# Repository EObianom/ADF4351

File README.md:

# ADF4351 Arduino Library & KiCad Hardware Design
| KiCad Hardware PCB Design | Software Output / RF Spectrum |
| :---: | :---: |
|  | https://github.com/user-attachments/assets/13627ffa-e069-458c-9974-3c6d26c1047d |

A complete open-source RF signal generation suite featuring a **lightweight C++ driver** and a **custom open-hardware PCB design in KiCad** for the Analog Devices ADF4351 wideband frequency synthesizer (35 MHz – 4.4 GHz).

### What This Project Provides
1. Software (Arduino Driver & Math Engine)
    - Register Calculation Engine: Automatically solves the complex Phase-Locked Loop (PLL) math to determine exact 32-bit values for hardware registers $R_0$ through $R_5$ across both Fractional-N and Integer-N modes.
    - Automatic Scaling: Handles RF output dividers (/1 to /64), dual-modulus prescalers (4/5 or 8/9), and GCD fraction reduction behind the scenes.
    - Hardware-Agnostic C++: Contains no hardcoded hardware SPI pins or board-specific hooks. Works seamlessly across all Arduino architectures, including AVR, ESP32, STM32, RP2040, Teensy, and SAMD, using standard SPI.h.
2. Hardware (KiCad Design Files)
    - Open Hardware Files: Complete schematics (.kicad_sch), 4-layer impedance-controlled PCB layouts (.kicad_pcb), and project files created in KiCad.
    - RF Output Network: Designed with proper high-frequency decoupling, low-noise power regulation, optimized loop filtering, and 50 Ω matched RF output traces with SMA connectivity for clean signal generation across the 35 MHz – 4.4 GHz spectrum.

## Table of Contents
- Features
- Installation
- Quick Start
- API Reference & Keyword Usage
  - Core Datatypes & Classes
  - Core Functions
  - Bulk Configuration
  - Register 5 Setters (Lock Detect & Initialization)
  - Register 4 Setters (RF Output & Power Controls)
  - Register 3 Setters (Clock Dividers & Modes)
  - Register 2 Setters (PLL & Charge Pump Controls)
  - Register 1 & 0 Setters (Prescaler & Phase Settings)
- Hardware Design & Variants
- Hardware Files & Production Assets
- License

## Features
- **Platform Agnostic:** Pure software calculation engine with zero hardware or architecture dependencies.
- **Dynamic PLL Solver:** Automates INT, FRAC, and MOD calculations with automated Euclidean GCD fraction reduction.
- **VCO & Divider Scaling:** Dynamically selects RF output dividers (/1 to /64) and prescalers (4/5 vs. 8/9).
- **Integrated Bitmask Safety:** All parameter setters perform bitwise masking to prevent register corruption.
- **KiCad Open Hardware Included:** Includes full schematic, PCB layout, and gerber files in the `hardware/` directory.

## Installation
### Via Arduino Library Manager
1. Open the Arduino IDE.
2. Go to Sketch → Include Library → Manage Libraries...
3. Search for ADF4351 and click Install.

### Manual Installation
1. Download the latest release .zip from GitHub.
2. In the Arduino IDE, go to Sketch → Include Library → Add .ZIP Library...
3. Select the downloaded .zip file.

## Quick Start
~~~
#include <Arduino.h>
#include "ADF4351.h"

const int CS_PIN = 10;
ADF4351 adf;

// Helper function to send 32-bit register words over hardware SPI
void writeRegister(uint32_t regData) {
    digitalWrite(CS_PIN, LOW);
    SPI.beginTransaction(SPISettings(5000000, MSBFIRST, SPI_MODE0));
    SPI.transfer32(regValue);
    SPI.endTransaction();
    digitalWrite(CS_PIN, HIGH);
    delayMicroseconds(1);
}

void setup() {
    Serial.begin(115200);
    pinMode(CS_PIN, OUTPUT);
    digitalWrite(CS_PIN, HIGH);
    SPI.begin();

    // 1. Configure synthesizer parameters (optional step; default is 25MHz ref clock)
    adf.setRefFreqHz(25000000);  // 25 MHz Reference
    adf.setOutputPower(3);       // +5 dBm Output Power

    // 2. Compute registers for target frequency (e.g., 433.92 MHz)
    uint32_t regs[6];
    if (adf.calculateRegisters(433920000ULL, regs)) {
        // Write registers R5 down to R0 in sequence (ADF4351 hardware requirement)
        for (int i = 5; i >= 0; i--) {
            writeRegister(regs[i]);
        }
        Serial.println(F("ADF4351 programmed successfully to 433.92 MHz!"));
    } else {
        Serial.println(F("Frequency target out of bounds or parameter error!"));
    }
}

void loop() {
    // Idle
}
~~~

## API Reference & Keyword Usage
### Core Datatypes & Classes
`ADF4351`

The primary class representing the ADF4351 synthesizer instance.
~~~
ADF4351 adf; // Instantiate with default configuration (25MHz TCXO/OCXO ref)
~~~
____
`Config`

A configuration structure containing all chip settings.
~~~
ADF4351::Config myConfig;
myConfig.refFreqHz = 10000000; // Set reference clock to 10 MHz
myConfig.outputPower = 2;      // Set power to +2 dBm
~~~

### Core Functions
`calculateRegisters(freqHz, outRegisters)`

Computes the 6 required 32-bit register values for a given frequency in Hertz.
- Parameters:
  - `freqHz (uint64_t)`: Target output frequency in Hz (35,000,000 to 4,400,000,000 Hz).
  - `outRegisters (uint32_t[6])`: Array to hold the resulting register words R0 through R5.
- Returns: bool – true if calculation succeeded; false if frequency is out of range or invalid.
~~~
uint32_t registers[6];
bool success = adf.calculateRegisters(1000000000ULL, registers); // 1.0 GHz
~~~

### Bulk Configuration
`setConfig(config)`

Overwrites the entire configuration struct in one operation.
~~~
ADF4351::Config cfg;
cfg.refFreqHz = 25000000;
cfg.outputPower = 3;
cfg.rfOutputEnable = 1;

adf.setConfig(cfg);
~~~
____
`getConfig()`

Retrieves the currently loaded configuration struct.
~~~
ADF4351::Config activeCfg = adf.getConfig();
Serial.print("Current Ref Freq: ");
Serial.println(activeCfg.refFreqHz);
~~~

### Individual Configuration Setting
#### Register 5 Setters
`setRefFreqHz(val)`

Sets the reference input frequency in Hz.
~~~
adf.setRefFreqHz(25000000); // 25 MHz Reference
~~~
___
`setLdPinMode(val)`

Configures the Lock Detect (LD) output pin mode (Bits [23:22], Mask: 0x03).
- 0: Low
- 1: Digital Lock Detect (Default)
- 2: Low
- 3: High
~~~
adf.setLdPinMode(1); // Digital Lock Detect
~~~

#### Register 4 Setters
`setFeedbackSelect(val)`

Selects VCO feedback signal source to N-counter (Bit [23], Mask: 0x01).
- 0: Divided (VCO output through divider)
- 1: Fundamental (VCO output directly; Default)
~~~
adf.setFeedbackSelect(1);
~~~
___
`setVcoPowerdown(val)`

Powers down the internal VCO (Bit [11], Mask: 0x01).
- 0: VCO Active
- 1: VCO Powered Down
~~~
adf.setVcoPowerdown(0);
~~~
___
`setMtld(val)`

Mute Till Lock Detect (Bit [10], Mask: 0x01).
- 0: Mute Disabled
- 1: Mute Enabled (RF output muted until PLL locks)
~~~
adf.setMtld(1);
~~~
___
`setAuxOutputSelect(val)`

Selects auxiliary RF output signal path (Bit [9], Mask: 0x01).
- 0: Divided Output
- 1: Fundamental Output
~~~
adf.setAuxOutputSelect(0);
~~~
___
`setAuxOutputEnable(val)`

Enables or disables auxiliary RF output pin (Bit [8], Mask: 0x01).
- 0: Disabled
- 1: Enabled
~~~
adf.setAuxOutputEnable(0);
~~~
___
`setAuxOutputPower(val)`

Configures auxiliary RF output power level (Bits [7:6], Mask: 0x03).
- 0: -4 dBm
- 1: -1 dBm
- 2: +2 dBm
- 3: +5 dBm
~~~
adf.setAuxOutputPower(0); // -4 dBm
~~~
___
`setRfOutputEnable(val)`

Main RF output power toggle (Bit [5], Mask: 0x01).
- 0: Output Disabled
- 1: Output Enabled
~~~
adf.setRfOutputEnable(1);
~~~
___
`setOutputPower(val)`

Sets main RF output power level (Bits [4:3], Mask: 0x03).
- 0: -4 dBm
- 1: -1 dBm
- 2: +2 dBm
- 3: +5 dBm
~~~
adf.setOutputPower(3); // +5 dBm maximum power
~~~

#### Register 3 Setters
`setBandSelectMode(val)`

Configures Band Select Clock logic mode (Bit [23], Mask: 0x01).
- 0: Low / Standard PFD frequency
- 1: High / Fast PFD frequency
~~~
adf.setBandSelectMode(0);
~~~
___
`setAbp(val)`

Anti-Backlash Pulse Width (Bit [22], Mask: 0x01).
- 0: 6 ns (Recommended for Fractional-N operation)
- 1: 3 ns (Recommended for Integer-N operation)
~~~
adf.setAbp(0);
~~~
___
`setChargeCancel(val)`

Charge pump cancellation control (Bit [21], Mask: 0x01).
- 0: Disabled
- 1: Enabled
~~~
adf.setChargeCancel(0);
~~~
___
`setCsr(val)`

Cycle Slip Reduction (Bit [18], Mask: 0x01).
- 0: Disabled
- 1: Enabled
~~~
adf.setCsr(0);
~~~
___
`setClkDivMode(val)`

Clock Divider Mode (Bits [16:15], Mask: 0x03).
- 0: Clock Divider Off
- 1: Fast Lock Enable
- 2: Resynchronization Enable
~~~
adf.setClkDivMode(0);
~~~
___
`setClkDivValue(val)`

12-bit clock divider value for fast-lock / resync (Bits [14:3], Mask: 0x0FFF).

Range: 0 to 4095.
~~~
adf.setClkDivValue(150);
~~~

#### Register 2 Setters
`setNoiseMode(val)`

Low Noise vs. Low Spur Mode configuration (Bits [30:29], Mask: 0x03).
- 0: Low Noise Mode
- 3: Low Spur Mode
~~~
adf.setNoiseMode(0); // Low noise mode
~~~
___
`setMuxout(val)`

Configures the multiplexer output pin function (Bits [28:26], Mask: 0x07).
- 0: Three-State Output
- 1: DVDD
- 2: DGND
- 3: R-Divider Output
- 4: N-Divider Output
- 5: Analog Lock Detect
- 6: Digital Lock Detect
~~~
adf.setMuxout(0);
~~~
___
`setReferenceDoubler(val)`

Enables input reference frequency multiplier (Bit [25], Mask: 0x01).
- 0: Disabled
- 1: Enabled (Doubles PFD frequency)
~~~
adf.setReferenceDoubler(0);
~~~
___
`setRdiv2(val)`

Reference Divide-by-2 toggle (Bit [24], Mask: 0x01).
- 0: Disabled
- 1: Divide reference clock by 2 before R-divider
~~~
adf.setRdiv2(0);
~~~
___
`setRDivider(val)`

10-bit Reference R-Divider value (Bits [23:14], Mask: 0x03FF). 

Range: 1 to 1023.
~~~
adf.setRDivider(1);
~~~
___
`setDoubleBuff(val)`

Double buffering control for Register 4 (Bit [13], Mask: 0x01).
- 0: Disabled
- 1: Enabled
~~~
adf.setDoubleBuff(0);
~~~
___
`setChargePumpCurr(val)`

Configures charge pump current setting (Bits [12:9], Mask: 0x0F).

Range: 0 (0.31 mA) to 15 (5.00 mA). Default 7 = 2.50 mA.
~~~
adf.setChargePumpCurr(7); // 2.50 mA
~~~
___
`setLdf(val)`

Lock Detect Functionality selection (Bit [8], Mask: 0x01).
- 0: Fractional-N Mode Lock Detect
- 1: Integer-N Mode Lock Detect
~~~
adf.setLdf(0);
~~~
___
`setLdp(val)`

Lock Detect Precision pulse threshold (Bit [7], Mask: 0x01).
- 0: 10 ns (40 consecutive cycles)
- 1: 6 ns (40 consecutive cycles)
~~~
adf.setLdp(0);
~~~
___
`setPdPolarity(val)`

Phase Detector Polarity (Bit [6], Mask: 0x01).
- 0: Negative (Non-inverting loop filter)
- 1: Positive (Inverting loop filter / active filter)
~~~
adf.setPdPolarity(1);
~~~
___
`setPowerDown(val)`

Software chip power-down mode (Bit [5], Mask: 0x01).
- 0: Disabled
- 1: Enabled
~~~
adf.setPowerDown(0);
~~~
___
`setCpThreeState(val)`

Charge Pump Three-State control (Bit [4], Mask: 0x01).
- 0: Disabled
- 1: Enabled
~~~
adf.setCpThreeState(0);
~~~
___
`setCounterReset(val)`

Resets internal N and R counters (Bit [3], Mask: 0x01).
- 0: Disabled
- 1: Enabled
~~~
adf.setCounterReset(0);
~~~

#### Register 1 & 0 Setters
`setAutoPrescaler(enable)`

Enables automated dynamic prescaler selection (4/5 vs. 8/9).

Can be _true_ or _false_.
~~~
adf.setAutoPrescaler(false);
~~~
___
`setPrescaler(val)`

Manually overrides the dual-modulus prescaler setting (Bit [27], Mask: 0x01). Automatically disables autoPrescaler.
- 0: 4/5 Prescaler
- 1: 8/9 Prescaler
~~~
adf.setPrescaler(1); // Manual 8/9 prescaler
~~~
___
`setPhaseAdjust(val)`

Phase adjustment control toggle (Bit [28], Mask: 0x01).
- 0: OFF
- 1: ON
~~~
adf.setPhaseAdjust(0);
~~~
___
`setPhaseValue(val)`

12-bit fractional phase word (Bits [26:15], Mask: 0x0FFF). Range: 0 to 4095.
~~~
adf.setPhaseValue(1);
~~~

## Hardware Design & Variants
The open-source hardware files located in the [`hardware/`](./hardware) directory provide a complete, 4-layer PCB design built in **KiCad**. Depending on your RF output and clock reference requirements, the hardware architecture accommodates three tailored board configurations:

* **Version 1 (Full Feature Output):** Breaks out all available differential RF output pairs (RFoutA+/A- and RFoutB+/B-) alongside an external SMA connector for a high-precision input reference clock.
* **Version 2 (Primary Differential):** Features the primary differential output pair (RFoutA+ and RFoutA-) with an external SMA input reference clock option.
* **Version 3 (Single-Ended & On-Board TCXO — Default):** Optimized for compact standalone operation with a single-ended RF output (RFoutA+) and an integrated 25MHz reference oscillator. *(Featured in the header image).*

---

## Hardware Files & Production Assets
All KiCad design, manufacturing, and documentation assets are structured in the [`hardware/`](./hardware) directory:

| Asset / File Name | Description |
| :--- | :--- |
| **`ADF4351.kicad_pro`** | Master KiCad project workspace file. |
| **`ADF4351.kicad_sch`** | Schematic diagram featuring low-noise LDO regulation, loop filter topology, and 50 Ω matching networks. |
| **`ADF4351.kicad_pcb`** | 4-layer controlled-impedance PCB layout. |
| **`Production/`** | Contains complete fabrication-ready **Gerbers**, Bill of Materials (**BOM**), and Component Placement List (**CPL**) for automated SMT assembly. |
| **`Figures/`** | High-resolution 3D renders of the assembled boards. |

## License
This library is released under the MIT License. Free to use, modify, and distribute in both open-source and commercial applications.

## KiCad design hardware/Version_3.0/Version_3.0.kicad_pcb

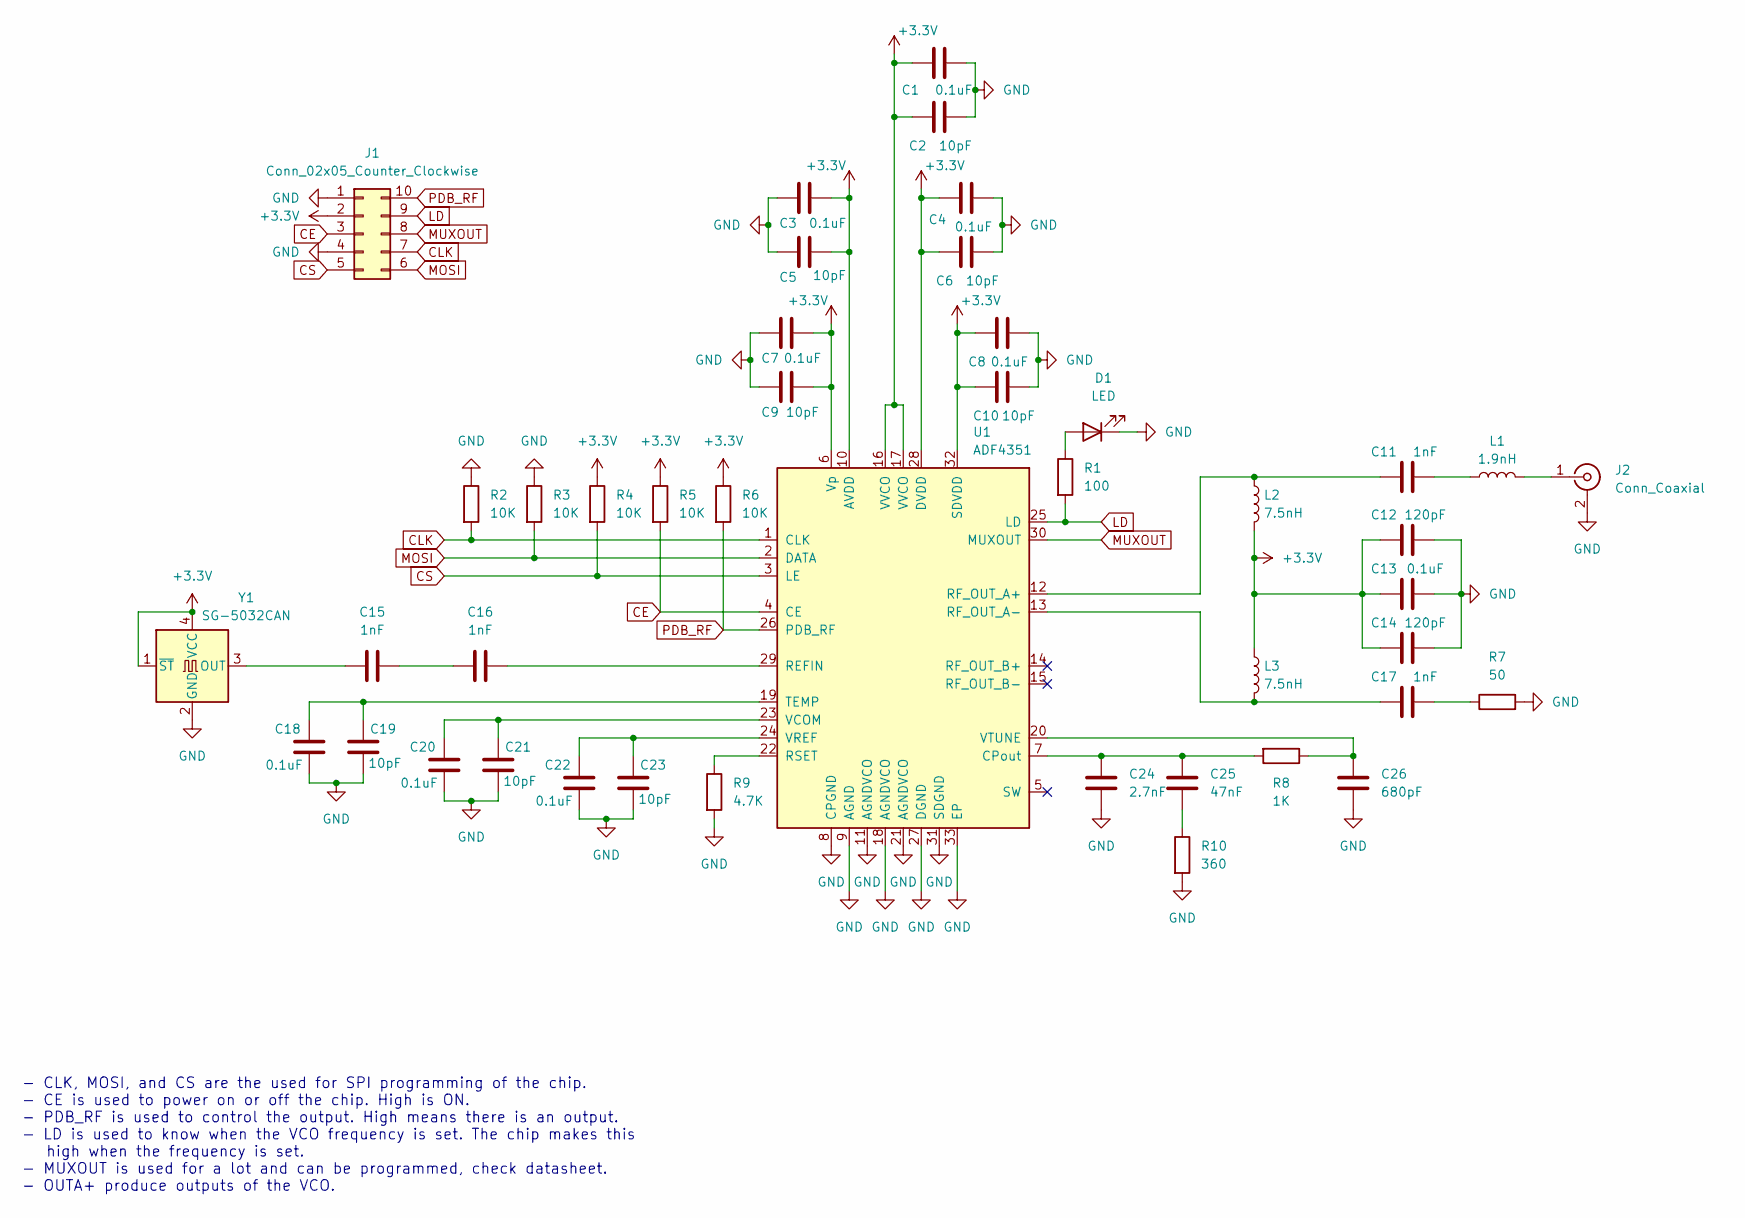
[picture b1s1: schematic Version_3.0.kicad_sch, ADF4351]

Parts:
C1, C3, C4, C7, C8, C13, C18, C20, C22: 0.1uF; C_0402_1005Metric
C2, C5, C6, C9, C10, C19, C21, C23: 10pF; C_0402_1005Metric
C11, C15, C16, C17: 1nF; C_0402_1005Metric
C12, C14: 120pF; C_0402_1005Metric
C24: 2.7nF; C_0402_1005Metric
C25: 47nF; C_0402_1005Metric
C26: 680pF; C_0402_1005Metric
D1: LED; LED_0402_1005Metric
J1: Conn_02x05_Counter_Clockwise; PinHeader_2x05_P2.54mm_Vertical
J2: Conn_Coaxial; SMA_Molex_73251-1153_EdgeMount_Horizontal
L1: 1.9nH; L_0402_1005Metric
L2, L3: 7.5nH; L_0402_1005Metric
R1: 100; R_0402_1005Metric
R2, R3, R4, R5, R6: 10K; R_0402_1005Metric
R7: 50; R_0402_1005Metric
R8: 1K; R_0402_1005Metric
R9: 4.7K; R_0402_1005Metric
R10: 360; R_0402_1005Metric
U1: ADF4351; LFCSP-32-1EP_5x5mm_P0.5mm_EP3.1x3.1mm
Y1: SG-5032CAN; Oscillator_SMD_SeikoEpson_SG8002LB-4Pin_5.0x3.2mm

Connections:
+3.3V: C1.2, C2.2, C3.2, C4.2, C5.2, C6.2, C7.2, C8.2, C9.2, C10.2, C12.2, C13.2, C14.2, J1.2, L2.2, L3.1, R4.1, R5.1, R6.1, U1.6 (Vp), U1.10 (AVDD), U1.16 (VVCO), U1.17 (VVCO), U1.28 (DVDD), U1.32 (SDVDD), Y1.1 (~ST), Y1.4 (VCC)
CE: J1.3, R5.2, U1.4 (CE)
CLK: J1.7, R2.2, U1.1 (CLK)
CS: J1.5, R4.2, U1.3 (LE)
GND: C1.1, C2.1, C3.1, C4.1, C5.1, C6.1, C7.1, C8.1, C9.1, C10.1, C12.1, C13.1, C14.1, C18.1, C19.1, C20.1, C21.1, C22.1, C23.1, C24.2, C26.2, D1.1 (K), J1.1, J1.4, J2.2 (Ext), R2.1, R3.1, R7.2, R9.2, R10.2, U1.8 (CPGND), U1.9 (AGND), U1.11 (AGNDVCO), U1.18 (AGNDVCO), U1.21 (AGNDVCO), U1.27 (DGND), U1.31 (SDGND), U1.33 (EP), Y1.2 (GND)
LD: J1.9, R1.2, U1.25 (LD)
MOSI: J1.6, R3.2, U1.2 (DATA)
MUXOUT: J1.8, U1.30 (MUXOUT)
unnamed: C11.1, L1.1
unnamed: C15.2, C16.1
unnamed: C17.1, R7.1
unnamed: C25.2, R10.1
unnamed: D1.2 (A), R1.1
unnamed: J2.1 (In), L1.2
unnamed: C24.1, C25.1, R8.2, U1.7 (CPout)
unnamed: C16.2, U1.29 (REFIN)
unnamed: C11.2, L2.1, U1.12 (RF_OUT_A+)
unnamed: C17.2, L3.2, U1.13 (RF_OUT_A-)
unnamed: R9.1, U1.22 (RSET)
unnamed: C18.2, C19.2, U1.19 (TEMP)
unnamed: C20.2, C21.2, U1.23 (VCOM)
unnamed: C22.2, C23.2, U1.24 (VREF)
unnamed: C26.1, R8.1, U1.20 (VTUNE)
unnamed: C15.1, Y1.3 (OUT)
PDB_RF: J1.10, R6.2, U1.26 (PDB_RF)

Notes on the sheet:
- CLK, MOSI, and CS are the used for SPI programming of the chip. - CE is used to power on or off the chip. High is ON. - PDB_RF is used to control the output. High means there is an output. - LD is used to know when the VCO frequency is set. The chip makes this high when the frequency is set. - MU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

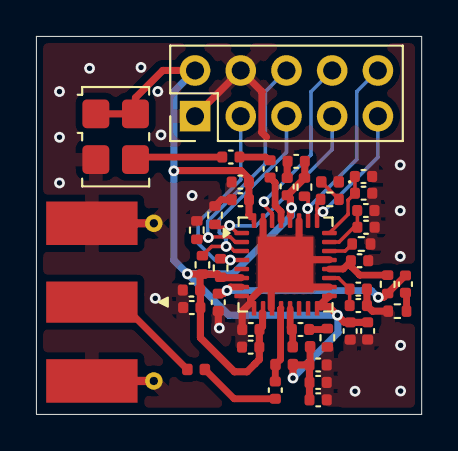
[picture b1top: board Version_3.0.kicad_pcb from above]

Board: 4 copper layers, 21.4 x 21.0 mm, 44 parts (0 on the bottom side), 25 nets.

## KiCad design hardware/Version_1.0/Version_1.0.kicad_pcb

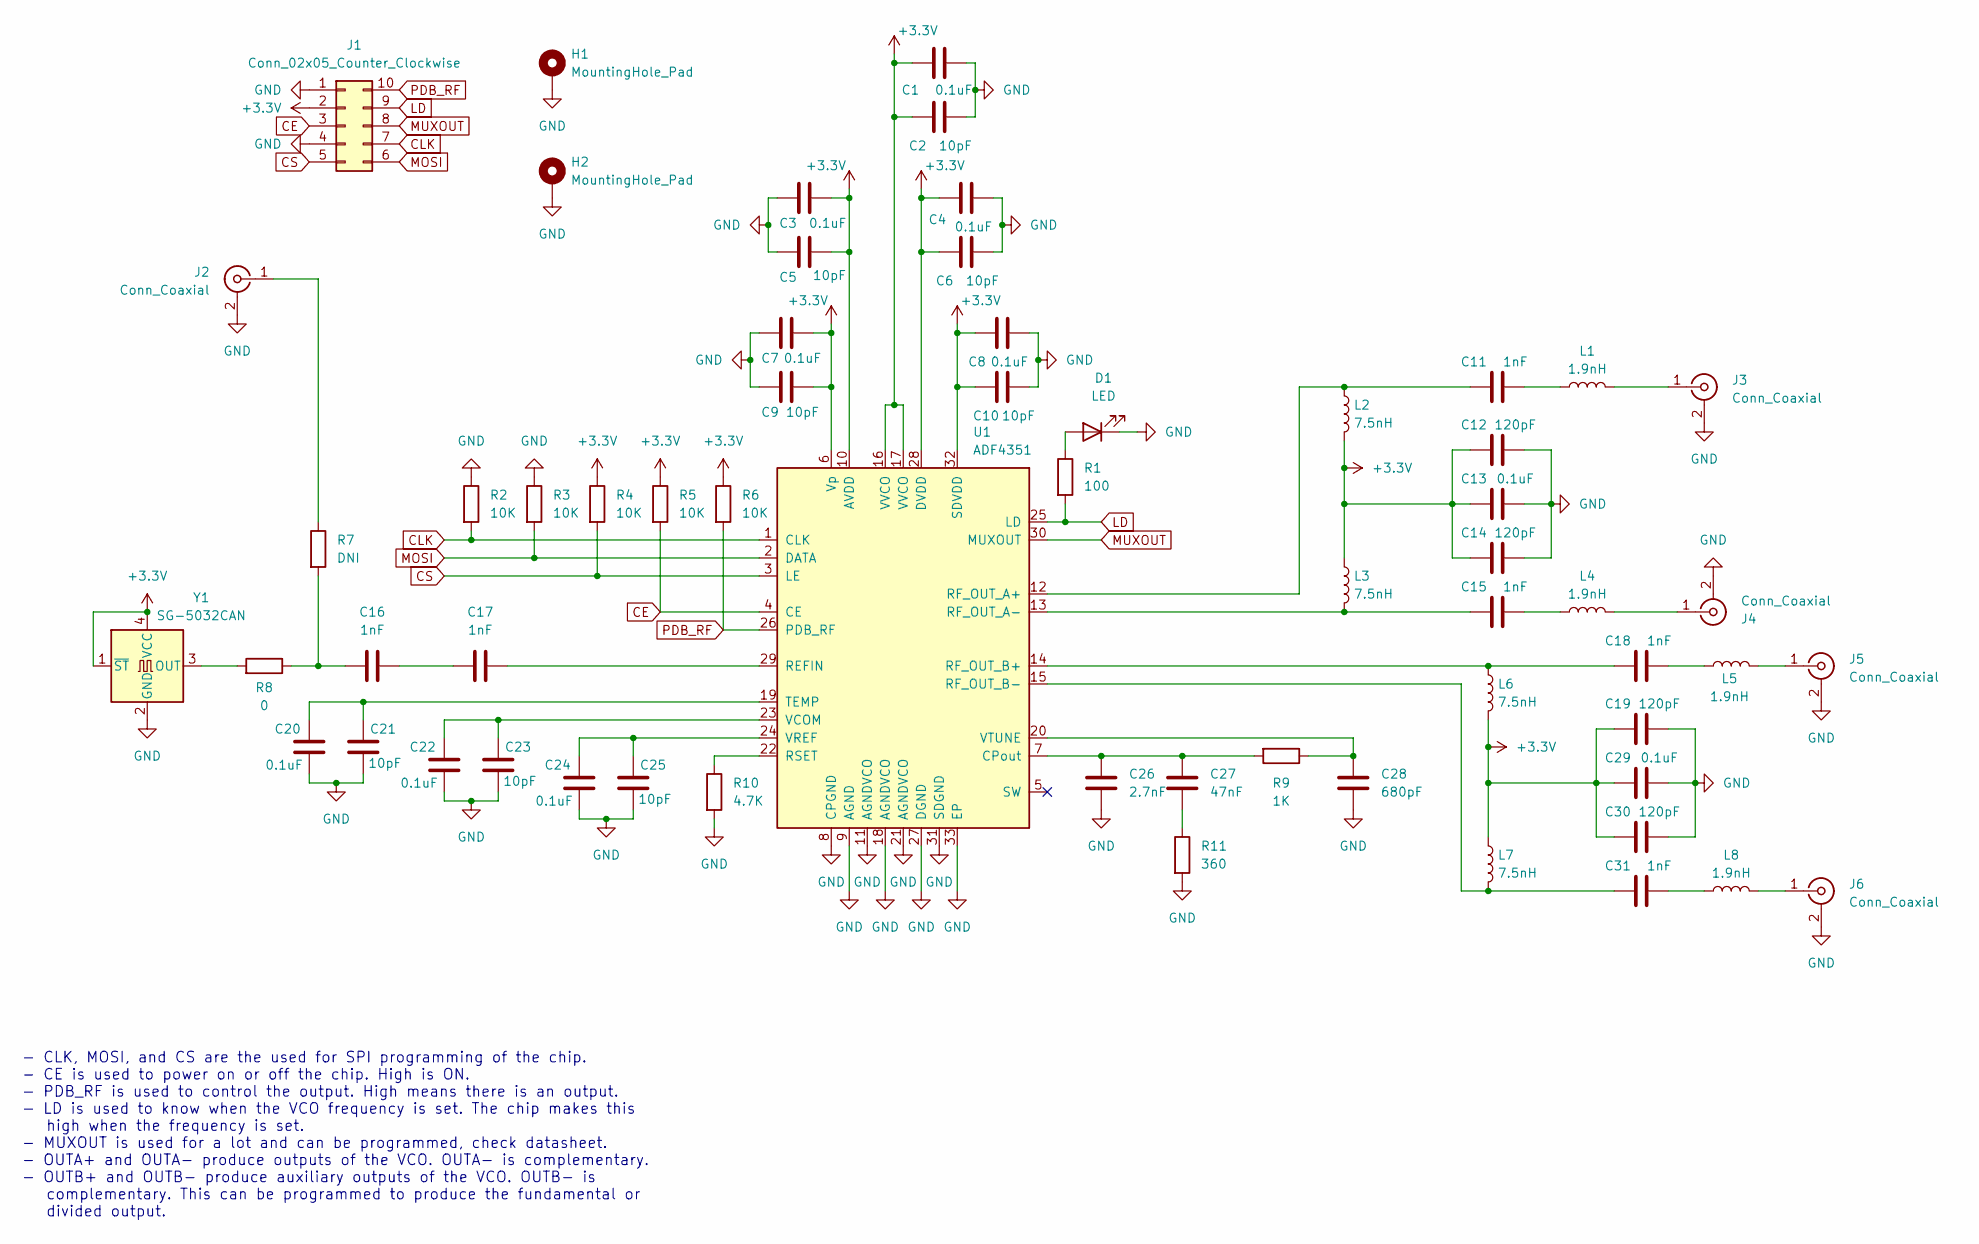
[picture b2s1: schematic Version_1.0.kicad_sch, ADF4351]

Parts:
C1, C3, C4, C7, C8, C13, C20, C22, C24, C29: 0.1uF; C_0402_1005Metric
C2, C5, C6, C9, C10, C21, C23, C25: 10pF; C_0402_1005Metric
C11, C15, C16, C17, C18, C31: 1nF; C_0402_1005Metric
C12, C14, C19, C30: 120pF; C_0402_1005Metric
C26: 2.7nF; C_0402_1005Metric
C27: 47nF; C_0402_1005Metric
C28: 680pF; C_0402_1005Metric
D1: LED; LED_0402_1005Metric
H1, H2: MountingHole_Pad; MountingHole_3.2mm_M3_Pad
J1: Conn_02x05_Counter_Clockwise; PinHeader_2x05_P2.54mm_Vertical
J2, J3, J4, J5, J6: Conn_Coaxial; SMA_Molex_73251-1153_EdgeMount_Horizontal
L1, L4, L5, L8: 1.9nH; L_0402_1005Metric
L2, L3, L6, L7: 7.5nH; L_0402_1005Metric
R1: 100; R_0402_1005Metric
R2, R3, R4, R5, R6: 10K; R_0402_1005Metric
R7: DNI; R_0402_1005Metric
R8: 0; R_0402_1005Metric
R9: 1K; R_0402_1005Metric
R10: 4.7K; R_0402_1005Metric
R11: 360; R_0402_1005Metric
U1: ADF4351; LFCSP-32-1EP_5x5mm_P0.5mm_EP3.1x3.1mm
Y1: SG-5032CAN; Oscillator_SMD_SeikoEpson_SG8002LB-4Pin_5.0x3.2mm

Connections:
+3.3V: C1.2, C2.2, C3.2, C4.2, C5.2, C6.2, C7.2, C8.2, C9.2, C10.2, C12.2, C13.2, C14.2, C19.2, C29.2, C30.2, J1.2, L2.2, L3.1, L6.2, L7.1, R4.1, R5.1, R6.1, U1.6 (Vp), U1.10 (AVDD), U1.16 (VVCO), U1.17 (VVCO), U1.28 (DVDD), U1.32 (SDVDD), Y1.1 (~ST), Y1.4 (VCC)
CE: J1.3, R5.2, U1.4 (CE)
CLK: J1.7, R2.2, U1.1 (CLK)
CS: J1.5, R4.2, U1.3 (LE)
GND: C1.1, C2.1, C3.1, C4.1, C5.1, C6.1, C7.1, C8.1, C9.1, C10.1, C12.1, C13.1, C14.1, C19.1, C20.1, C21.1, C22.1, C23.1, C24.1, C25.1, C26.2, C28.2, C29.1, C30.1, D1.1 (K), H1.1 (1_1), H2.1 (1_1), J1.1, J1.4, J2.2 (Ext), J3.2 (Ext), J4.2 (Ext), J5.2 (Ext), J6.2 (Ext), R2.1, R3.1, R10.2, R11.2, U1.8 (CPGND), U1.9 (AGND), U1.11 (AGNDVCO), U1.18 (AGNDVCO), U1.21 (AGNDVCO), U1.27 (DGND), U1.31 (SDGND), U1.33 (EP), Y1.2 (GND)
LD: J1.9, R1.2, U1.25 (LD)
MOSI: J1.6, R3.2, U1.2 (DATA)
MUXOUT: J1.8, U1.30 (MUXOUT)
unnamed: C11.1, L1.1
unnamed: C15.1, L4.1
unnamed: C16.1, R7.2, R8.1
unnamed: C16.2, C17.1
unnamed: C18.1, L5.1
unnamed: C27.2, R11.1
unnamed: C31.1, L8.1
unnamed: D1.2 (A), R1.1
unnamed: J2.1 (In), R7.1
unnamed: J3.1 (In), L1.2
unnamed: J4.1 (In), L4.2
unnamed: J5.1 (In), L5.2
unnamed: J6.1 (In), L8.2
unnamed: C26.1, C27.1, R9.2, U1.7 (CPout)
unnamed: C17.2, U1.29 (REFIN)
unnamed: C11.2, L2.1, U1.12 (RF_OUT_A+)
unnamed: C15.2, L3.2, U1.13 (RF_OUT_A-)
unnamed: C18.2, L6.1, U1.14 (RF_OUT_B+)
unnamed: C31.2, L7.2, U1.15 (RF_OUT_B-)
unnamed: R10.1, U1.22 (RSET)
unnamed: C20.2, C21.2, U1.19 (TEMP)
unnamed: C22.2, C23.2, U1.23 (VCOM)
unnamed: C24.2, C25.2, U1.24 (VREF)
unnamed: C28.1, R9.1, U1.20 (VTUNE)
unnamed: R8.2, Y1.3 (OUT)
PDB_RF: J1.10, R6.2, U1.26 (PDB_RF)

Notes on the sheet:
- CLK, MOSI, and CS are the used for SPI programming of the chip. - CE is used to power on or off the chip. High is ON. - PDB_RF is used to control the output. High means there is an output. - LD is used to know when the VCO frequency is set. The chip makes this high when the frequency is set. - MU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

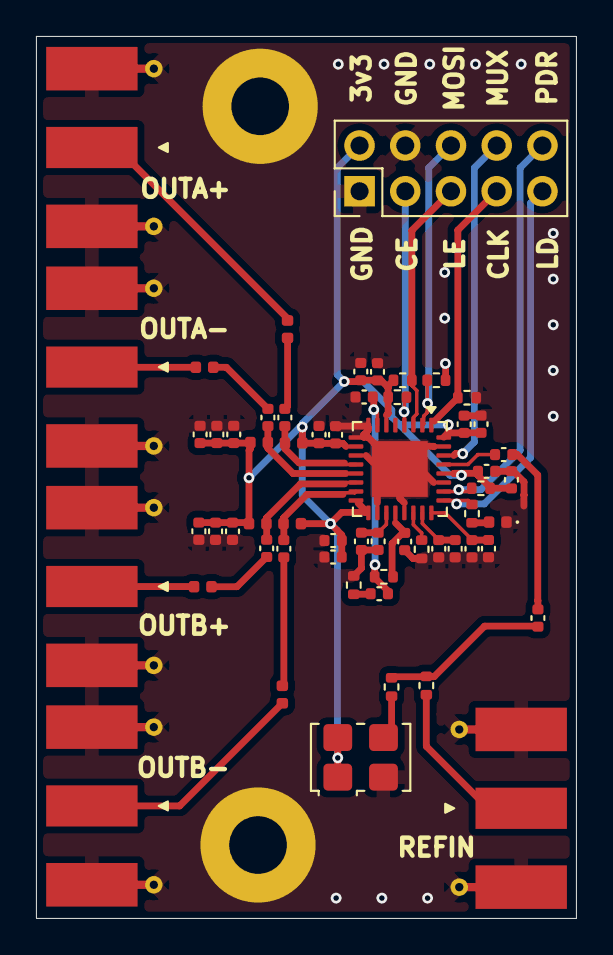
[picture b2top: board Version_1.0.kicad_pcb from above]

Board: 4 copper layers, 30.0 x 49.0 mm, 61 parts (0 on the bottom side), 34 nets.
